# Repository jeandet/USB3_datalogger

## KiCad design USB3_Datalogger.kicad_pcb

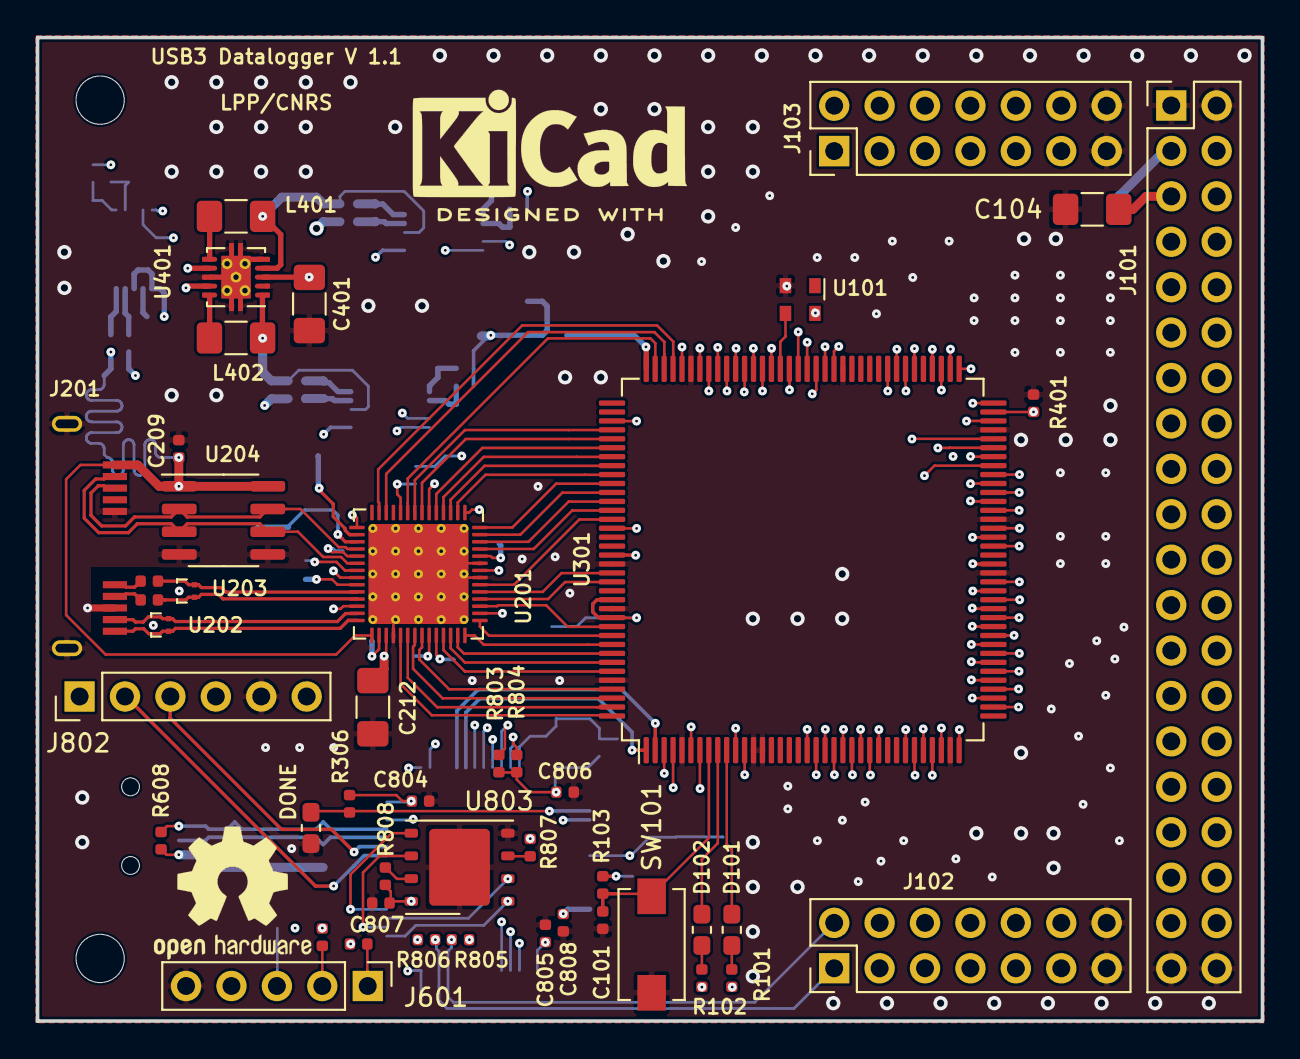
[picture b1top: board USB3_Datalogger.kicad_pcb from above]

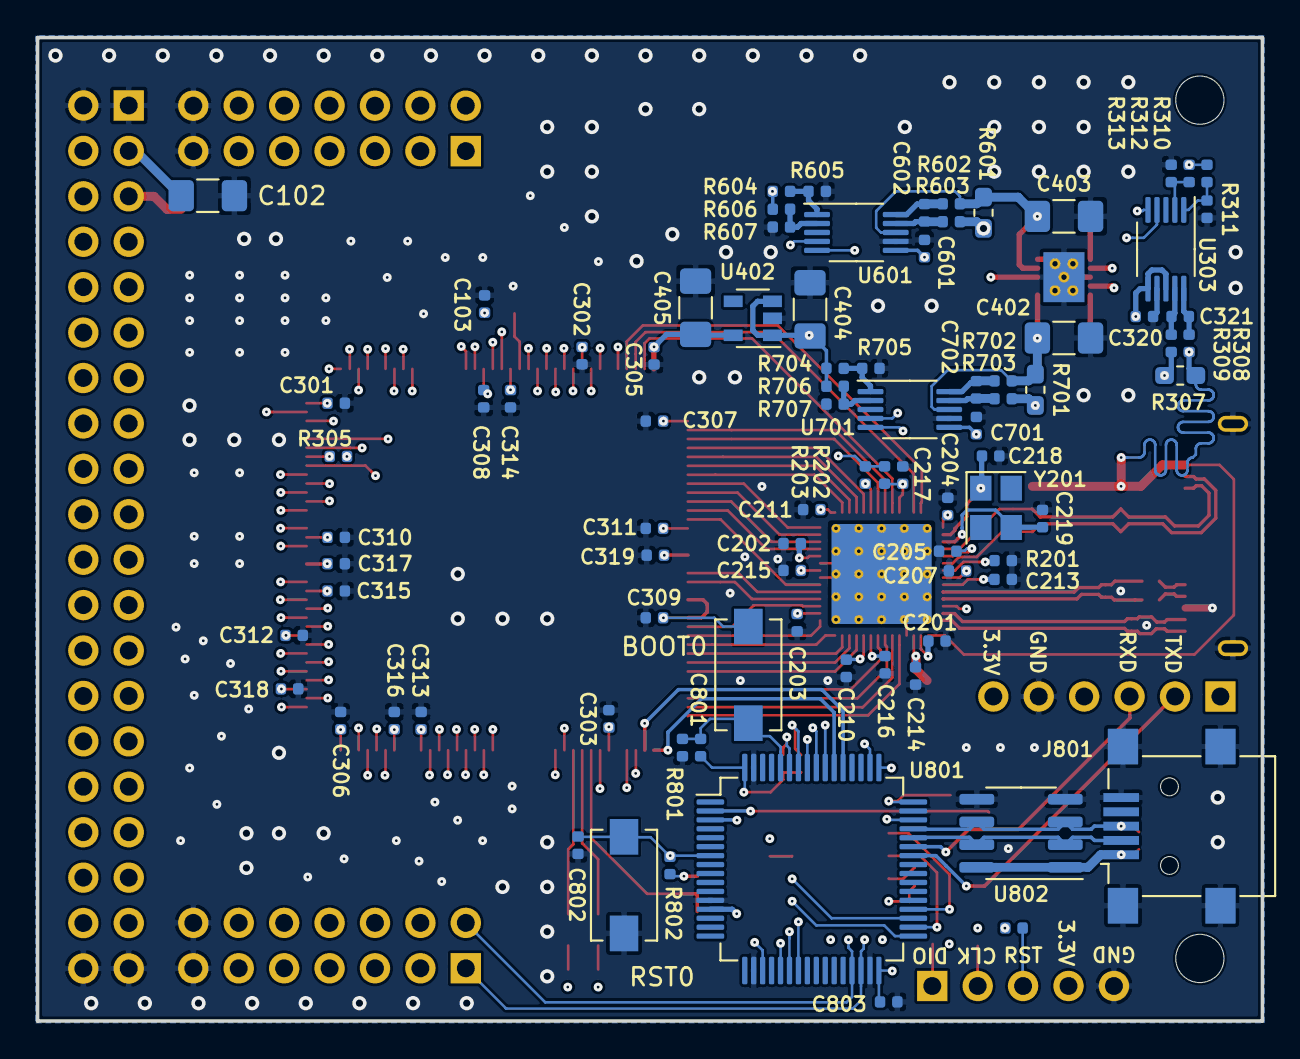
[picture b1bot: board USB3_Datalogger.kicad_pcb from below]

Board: 6 copper layers, 68.5 x 55.0 mm, 136 parts (86 on the bottom side), 155 nets.

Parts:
BOOT0: SW_Push; SW_SPST_EVQPE1
C101, C103, C201, C202, C203, C204, C205, C206, C207, C208, C209, C210, C211, C213, C214, C215, C216, C217, C301, C302, C303, C305, C306, C307, C308, C309, C310, C311, C312, C313, C314, C315, C316, C317, C318, C319, C320, C601, C701, C801, C802, C803, C804, C805, C806, C807, C808: 100nF; C_0402_1005Metric
C102, C104: 10µF; C_1206_3216Metric_Pad1.42x1.75mm_HandSolder
C212: 4.7µF; C_1206_3216Metric_Pad1.42x1.75mm_HandSolder
C218, C219: 18pF; C_0402_1005Metric
C321, C602, C702: 10pF; C_0402_1005Metric
C401, C402, C403, C404, C405: 10uF; C_1206_3216Metric_Pad1.42x1.75mm_HandSolder
D101, D102: LED; R_0603_1608Metric_Pad1.05x0.95mm_HandSolder
DONE401: LED; R_0603_1608Metric_Pad1.05x0.95mm_HandSolder
H101, H102: MountingHole; MountingHole_2.7mm_M2.5
J101: Conn_02x20_Odd_Even; PinHeader_2x20_P2.54mm_Vertical
J102, J103: Conn_02x07_Odd_Even; PinHeader_2x07_P2.54mm_Vertical
J201: USB3-micro; GSB343K33HR
J601: Conn_01x05; PinHeader_1x05_P2.54mm_Vertical
J801: USB_B_Mini; USB_Mini-B_Lumberg_2486_01_Horizontal
J802: Conn_01x06; PinHeader_1x06_P2.54mm_Vertical
L401, L402: 2.2uH; L_1206_3216Metric_Pad1.42x1.75mm_HandSolder
LOGO101: Logo_Open_Hardware_Small; OSHW-Logo2_9.8x8mm_SilkScreen
LOGO102: Logo_Open_Hardware_Small; KiCad-Logo2_6mm_SilkScreen
R101, R102, R103, R306, R801, R802, R803, R804, R805, R806: 2K2; R_0402_1005Metric
R201: 1.6k; R_0402_1005Metric
R202, R203, R305, R310, R311, R312, R313, R401, R604, R605, R606, R607, R704, R705, R706, R707, R807, R808: 10k; R_0402_1005Metric
R307, R601, R701: 100m; C_0603_1608Metric_Pad1.05x0.95mm_HandSolder
R308, R309, R602, R603, R702, R703: 10; R_0402_1005Metric
R608: 4k7; R_0402_1005Metric
R609, R610, R611: 22; R_0402_1005Metric
RST0: SW_Push; SW_SPST_EVQPE1
SW101: SW_Push; SW_SPST_EVQPE1
U101: ASDMB-xxxMHz; Oscillator_SMD_Abracon_ASDMB-4Pin_2.5x2.0mm
U201: FT600; QFN-56-1EP_7x7mm_P0.4mm_EP5.6x5.6mm_ThermalVias
U202, U203: TPD2EUSB30; Texas_DRT-3
U204, U802: USB6B1; SOIC-8_3.9x4.9mm_P1.27mm
U301: ICE40HX1K-4K-TQ144; TQFP-144_20x20mm_P0.5mm
U303, U601, U701: INA226; VSSOP-10_3x3mm_P0.5mm
U401: tps6240x; Texas_S-PVSON-N10_ThermalVias
U402: TLV73325PDBV; SOT-23-5
U801: STM32F103RCTx; LQFP-64_10x10mm_P0.5mm
U803: W25Q32JVZP; WSON-8-1EP_6x5mm_P1.27mm_EP3.4x4.3mm
Y201: 30MHz; Crystal_SMD_3225-4Pin_3.2x2.5mm

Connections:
/2.5V: C305.1, C405.1, U301.108, U402.5
/Ext_I2C_SCL: J102.2, R805.2, U801.29
/Ext_I2C_SDA: J102.1, R806.2, U801.30
/FPGA/DATA_0: U201.33, U301.144
/FPGA/DATA_1: U201.34, U301.143
/FPGA/DATA_2: U201.35, U301.142
/FPGA/DATA_3: U201.36, U301.141
/FPGA/DATA_4: U201.39, U301.139
/FPGA/DATA_5: U201.40, U301.138
/FPGA/DATA_6: U201.41, U301.137
/FPGA/DATA_7: U201.42, U301.136
/FPGA/DATA_8: U201.45, U301.134
/FPGA/DATA_9: U201.46, U301.129
/FPGA/DATA_10: U201.47, U301.128
/FPGA/DATA_11: U201.48, U301.122
/FPGA/DATA_12: U201.53, U301.121
/FPGA/DATA_13: U201.54, U301.120
/FPGA/DATA_14: U201.55, U301.119
/FPGA/DATA_15: U201.56, U301.118
/FPGA/FIFO_GPIO_0: U201.12, U301.106
/FPGA/FIFO_GPIO_1: U201.13, U301.105
/FPGA/FLASH_CDONE: DONE401.2, R306.2, U301.65, U801.2
/FPGA/FLASH_CLK: U301.70, U801.55
/FPGA/FLASH_MISO: U301.67, U801.56
/FPGA/FLASH_MOSI: U301.68, U801.57
/FPGA/FLASH_SS: R401.1, U301.71, U801.50
/FPGA/FLASH_~CRESET: R305.2, U301.66, U801.3
/FPGA/~FIFO_OE: U201.9, U301.107
/FPGA/~FIFO_RD: U201.8, U301.112
/FPGA/~FIFO_RXF: U201.5, U301.114
/FPGA/~FIFO_TXE: U201.4, U301.115
/FPGA/~FIFO_WR: U201.7, U301.113
/IOB_1: J101.33, U301.38
/IOB_2: J101.34, U301.39
/IOB_3: J101.31, U301.41
/IOB_4: J101.32, U301.42
/IOB_5: J101.29, U301.43
/IOB_6: J101.30, U301.44
/IOB_7: J101.27, U301.45
/IOB_8: J101.28, U301.47
/IOB_9: J101.25, U301.48
/IOB_10: J101.26, U301.49
/IOB_11: J101.23, U301.50
/IOB_12: J101.24, U301.52
/IOB_13: J101.21, U301.56
/IOB_14: J101.22, U301.58
/IOB_15: J101.19, U301.60
/IOB_16: J101.20, U301.61
/IOB_17: J101.17, U301.62
/IOB_18: J101.18, U301.63
/IOB_19: J101.15, U301.64
/IOL_0: U301.1, U801.54
/IOL_1: U301.2, U801.53
/IOL_2: U301.3, U801.23
/IOL_3: U301.4, U801.22
/IOL_4: U301.7, U801.21
/IOL_5: C101.1, R103.2, SW101.2, U301.8
/IOL_6: D102.1, U301.9
/IOL_7: D101.1, U301.10
/IOL_8: J102.3, U301.11
/IOL_9: J102.4, U301.12
/IOL_10: J102.5, U301.19
/IOL_11: J102.6, U301.20
/IOL_12: J102.7, U301.21
/IOL_13: J102.8, U301.22
/IOL_14: J102.9, U301.23
/IOL_15: J102.10, U301.24
/IOL_16: J102.11, U301.25
/IOL_17: J102.12, U301.26
/IOL_20: J101.37, U301.31
/IOL_21: J101.38, U301.32
/IOL_22: J101.35, U301.33
/IOL_23: J101.36, U301.34
/IOR_0: J101.16, U301.73
/IOR_1: J101.13, U301.74
/IOR_2: J101.14, U301.75
/IOR_3: J101.11, U301.76
/IOR_4: J101.12, U301.78
/IOR_5: J101.9, U301.79
/IOR_6: J101.10, U301.80
/IOR_7: J101.7, U301.81
/IOR_8: J101.8, U301.87
/IOR_9: J103.11, U301.88
/IOR_10: J103.12, U301.90
/IOR_11: J103.9, U301.91
/IOR_12: U101.3, U301.93
/IOR_13: J103.10, U301.94
/IOR_14: J103.7, U301.95
/IOR_15: J103.8, U301.96
/IOR_16: J103.5, U301.97
/IOR_17: J103.6, U301.98
/IOR_18: J103.3, U301.99
/IOR_19: J103.4, U301.101
/IOR_20: J103.1, U301.102
/IOR_21: J103.2, U301.104
/Power/1V2Monitor/A0: R606.2, R607.1, U601.2
/Power/1V2Monitor/A1: R604.2, R605.1, U601.1
/Power/3V3Monitor/A0: R706.2, R707.1, U701.2
/Power/3V3Monitor/A1: R704.2, R705.1, U701.1
/Power/#1.2V: C403.1, L401.2, R601.1, R602.2, U401.4, U601.8
/Power/#3.3V: C402.1, L402.2, R701.1, R702.2, U401.1, U701.8
/STM32/BOOT0: BOOT0.2, C801.2, R801.1, U801.60
/STM32/FLASH_CLK: U801.34, U803.6
/STM32/FLASH_MISO: U801.35, U803.2
/STM32/FLASH_MOSI: U801.36, U803.5
/STM32/FLASH_~CS: U801.33, U803.1
/STM32/FLASH_~HOLD: R808.2, U803.7
/STM32/FLASH_~WP: R807.2, U803.3
/STM32/Int_SCL: R803.2, U303.5, U601.5, U701.5, U801.58
/STM32/Int_SDA: R804.2, U303.4, U601.4, U701.4, U801.59
/STM32/RESET: C802.1, R611.2, R802.2, RST0.1, U801.7
/STM32/SWCLK: R610.2, U801.49
/STM32/SWDIO: R609.2, U801.46
/STM32/UART1_RX: J802.3, U801.43
/STM32/UART1_TX: J802.2, U801.42
/STM32/USB_D+: J801.3, R608.2, U801.45, U802.3, U802.6
/STM32/USB_D-: J801.2, U801.44, U802.2, U802.7
/STM32/VBUS: J801.1, R608.1, U802.1, U802.8
/USB3/5VUSBMON/A0: R312.2, R313.1, U303.2
/USB3/5VUSBMON/A1: R310.2, R311.1, U303.1
/USB3/BE_0: U201.2, U301.117
/USB3/BE_1: U201.3, U301.116
/USB3/CLK: U201.43, U301.135
/USB3/SSRX+: J201.10, U201.28, U202.1
/USB3/SSRX-: J201.9, U201.27, U202.2
/USB3/SSTX+: C206.2, J201.7
/USB3/SSTX-: C208.2, J201.6
/USB3/TOD+: C206.1, U201.25, U203.1
/USB3/TOD-: C208.1, U201.24, U203.2
/USB3/USB2_D+: J201.3, U201.18, U204.2, U204.7
/USB3/USB2_D-: J201.2, U201.20, U204.3, U204.6
/USB3/VBUS: C209.1, C320.1, J201.1, R307.1, R308.2, R310.1, R312.1, U201.29, U204.1, U204.8, U303.6, U303.8
/USB3/VD10: C211.1, C212.1, C213.1, C214.1, C215.1, C216.1, U201.1, U201.23, U201.26, U201.31, U201.37, U201.50
/USB_5V: C102.1, C401.1, C404.1, C601.1, C701.1, J101.3, J101.4, R307.2, R309.2, R604.1, R606.1, R704.1, R706.1, U401.3, U401.7, U401.9, U402.1, U402.3, U601.6, U701.6
GND: C101.2, C102.2, C103.2, C104.2, C201.2, C202.2, C203.2, C204.2, C205.2, C207.2, C209.2, C210.2, C211.2, C212.2, C213.2, C214.2, C215.2, C216.2, C217.2, C218.1, C219.1, C301.2, C302.2, C303.2, C305.2, C306.2, C307.2, C308.2, C309.2, C310.2, C311.2, C312.2, C313.2, C314.2, C315.2, C316.2, C317.2, C318.2, C319.2, C320.2, C401.2, C402.2, C403.2, C404.2, C405.2, C601.2, C701.2, C802.2, C803.2, C804.2, C805.2, C806.2, C807.2, C808.2, DONE401.1, J101.1, J101.2, J101.39, J101.40, J102.13, J102.14, J103.13, J103.14, J201.5, J201.8, J201.11, J601.5, J801.5, J801.6, J802.5, R201.1, R311.2, R313.2, R401.2, R605.2, R607.2, R705.2, R707.2, R801.2, RST0.2, SW101.1, U101.2, U201.32, U201.49, U201.51, U201.57, U202.3, U203.3, U204.4, U204.5, U301.5, U301.13, U301.14, U301.35, U301.53, U301.59, U301.69, U301.86, U301.103, U301.127, U301.132, U301.140, U303.7, U401.2, U401.5, U401.8, U401.11, U402.2, U601.7, U701.7, U801.12, U801.18, U801.31, U801.47, U801.63, U802.4, U802.5, U803.4, U803.9
unnamed: C217.1, R202.2, U201.10
unnamed: C218.2, U201.16, Y201.1
unnamed: C219.2, U201.17, Y201.3
unnamed: C321.1, R308.1, U303.10
unnamed: C321.2, R309.1, U303.9
unnamed: C602.1, R602.1, U601.10
unnamed: C602.2, R603.1, U601.9
unnamed: C702.1, R702.1, U701.10
unnamed: C702.2, R703.1, U701.9
unnamed: D101.2, R101.2
unnamed: D102.2, R102.2
unnamed: J601.1, R609.1
unnamed: J601.2, R610.1
unnamed: J601.3, R611.1
unnamed: L401.1, U401.6
unnamed: L402.1, U401.10
unnamed: R201.2, U201.21
unnamed: R203.2, U201.6
VCC: C306.1, C307.1, C313.1, C314.1, C315.1, C317.1, C318.1, C319.1, R601.2, R603.2, U301.27, U301.36, U301.40, U301.51, U301.54, U301.92, U301.111, U301.126
VCCIO_0: BOOT0.1, C103.1, C104.1, C201.1, C202.1, C203.1, C204.1, C205.1, C207.1, C210.1, C301.1, C302.1, C303.1, C308.1, C309.1, C310.1, C311.1, C312.1, C316.1, C801.1, C803.1, C804.1, C805.1, C806.1, C807.1, C808.1, J101.5, J101.6, J601.4, J802.6, R101.1, R102.1, R103.1, R202.1, R203.1, R305.1, R306.1, R701.2, R703.2, R802.1, R803.1, R804.1, R805.1, R806.1, R807.1, R808.1, U101.4, U201.15, U201.19, U201.22, U201.30, U201.38, U201.44, U201.52, U301.6, U301.30, U301.46, U301.57, U301.72, U301.89, U301.100, U301.123, U301.131, U301.133, U801.13, U801.19, U801.32, U801.48, U801.64, U803.8

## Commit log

2020-02-17 First init, USB3 layout + FPGA done
2020-02-18 PCB complete, ready for review.
2020-02-18 Added Oscillator for the FPGA and updated PCB to match Eurocircuits rules.
2020-02-19 Made the board compatible with HX4K variant
2020-02-24 Added STM32F1 as FPGA companion
2020-02-24 STM32 connected VDDA to 3.3V
2020-02-24 Added many GND vias
2020-03-04 Last cleanups before PCB manufacturing
2020-07-22 Many fixes for 1.1
    - fixed FTDI power supply mistake(3.3V was floating)
    - updated resistors footprints
    - updated push button footprints
    - connected STM32 UART 1 to programming header
    - added pull up resistor on USB D+ for STM32
    - added 10uF capacitors on 5V and 3.3V near daughter board connectors
2020-07-22 Added SWD header to flash and debug STM32 chip
2020-07-23 Moved FPGA signals to inner layers, many other fixes
